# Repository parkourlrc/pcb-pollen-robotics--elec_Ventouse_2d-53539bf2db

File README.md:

# "Ventouse_2d" Electronic Board

"Ventouse_2d" is build from "Themis" as it aims on driving Orbita 2 Dofs. It is paired with boards "Poulpe_2d" that controls 2 BLDC Motors.

## Basically
 - Primarly designed for Reachy 2 gamma.
 - Powered in 24V.
 - Designed with KiCAD 7.

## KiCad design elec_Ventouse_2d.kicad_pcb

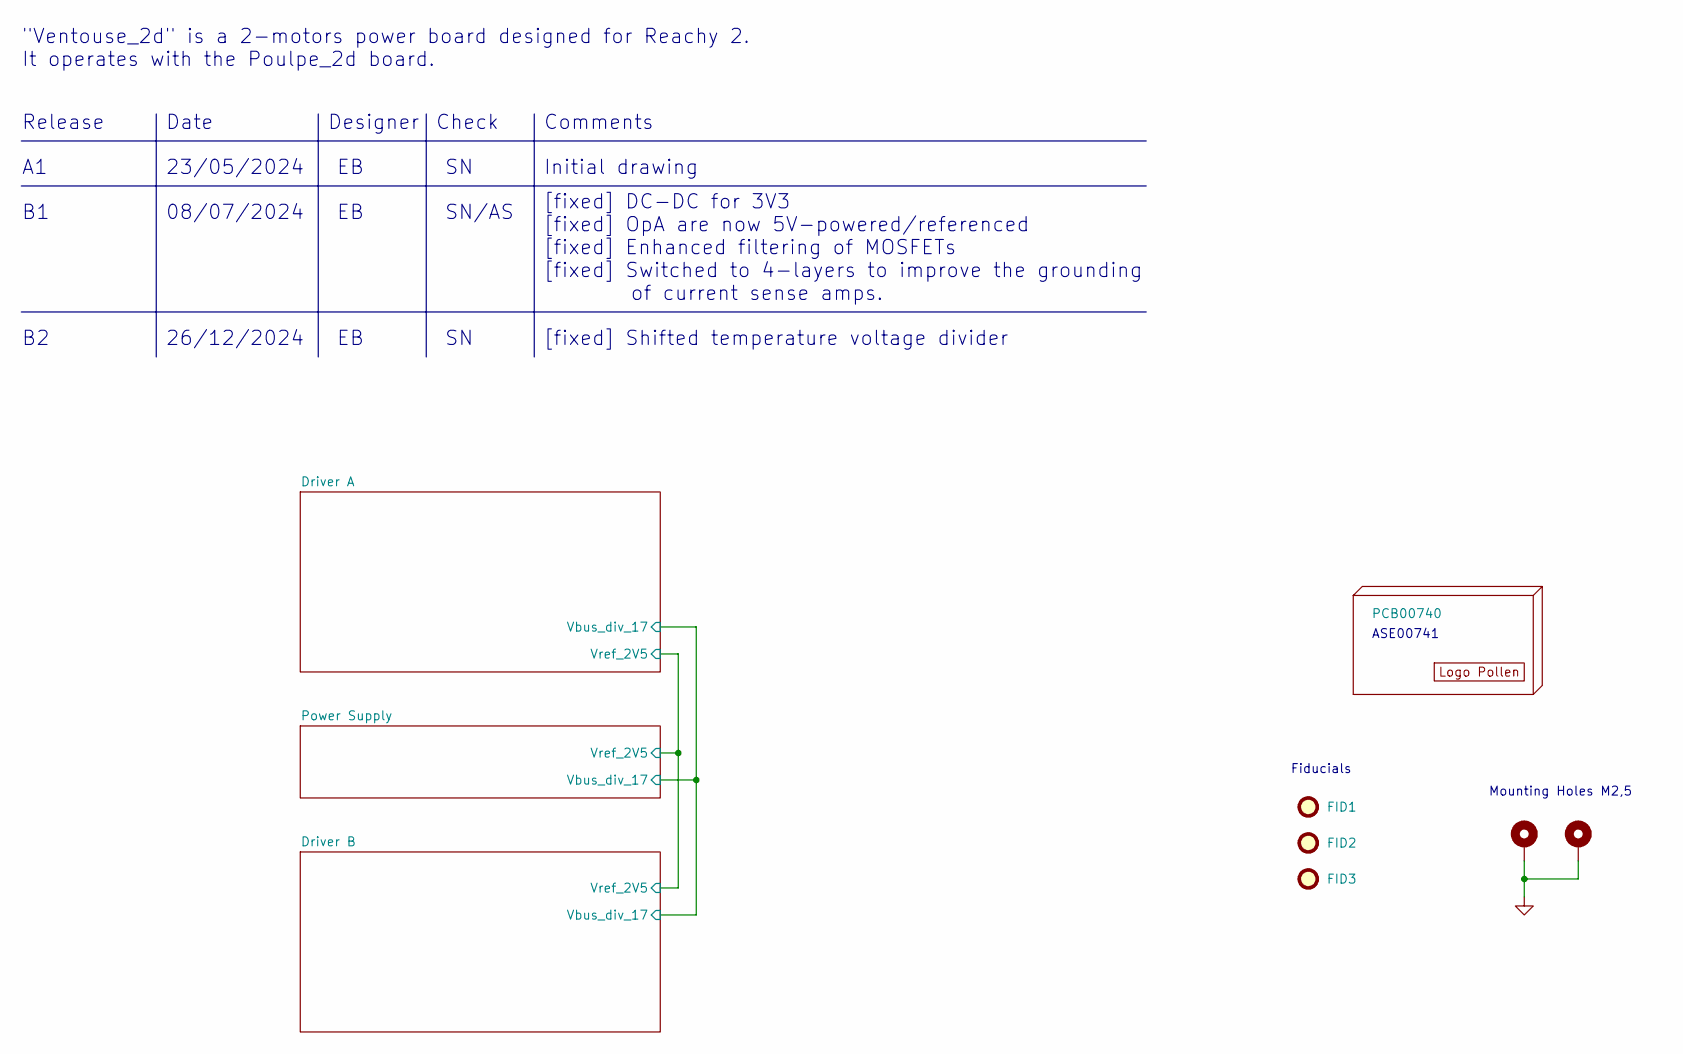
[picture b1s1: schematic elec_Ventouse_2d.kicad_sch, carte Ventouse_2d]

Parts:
FID1, FID2, FID3: DNP Fiducial; Fiducial_1mm_Mask2mm
H1, H2: MountingHole_Pad; MountingHole_2.7mm_M2.5_ISO14580_Pad_TopBottom
H4: PCB00740
H5: DNP Logo Pollen 2021; Logo_Pollen_2021_sq

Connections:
GND: H1.1, H2.1; also elsewhere on the board

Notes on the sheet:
Mounting Holes M2,5
Date
Check
Release
Fiducials
ASE00741
08/07/2024
SN/AS
[fixed] DC-DC for 3V3 [fixed] OpA are now 5V-powered/referenced [fixed] Enhanced filtering of MOSFETs [fixed] Switched to 4-layers to improve the grounding of current sense amps.
Initial drawing
[fixed] Shifted temperature voltage divider
"Ventouse_2d" is a 2-motors power board designed for Reachy 2. It operates with the Poulpe_2d board.
Designer
Comments
23/05/2024
26/12/2024

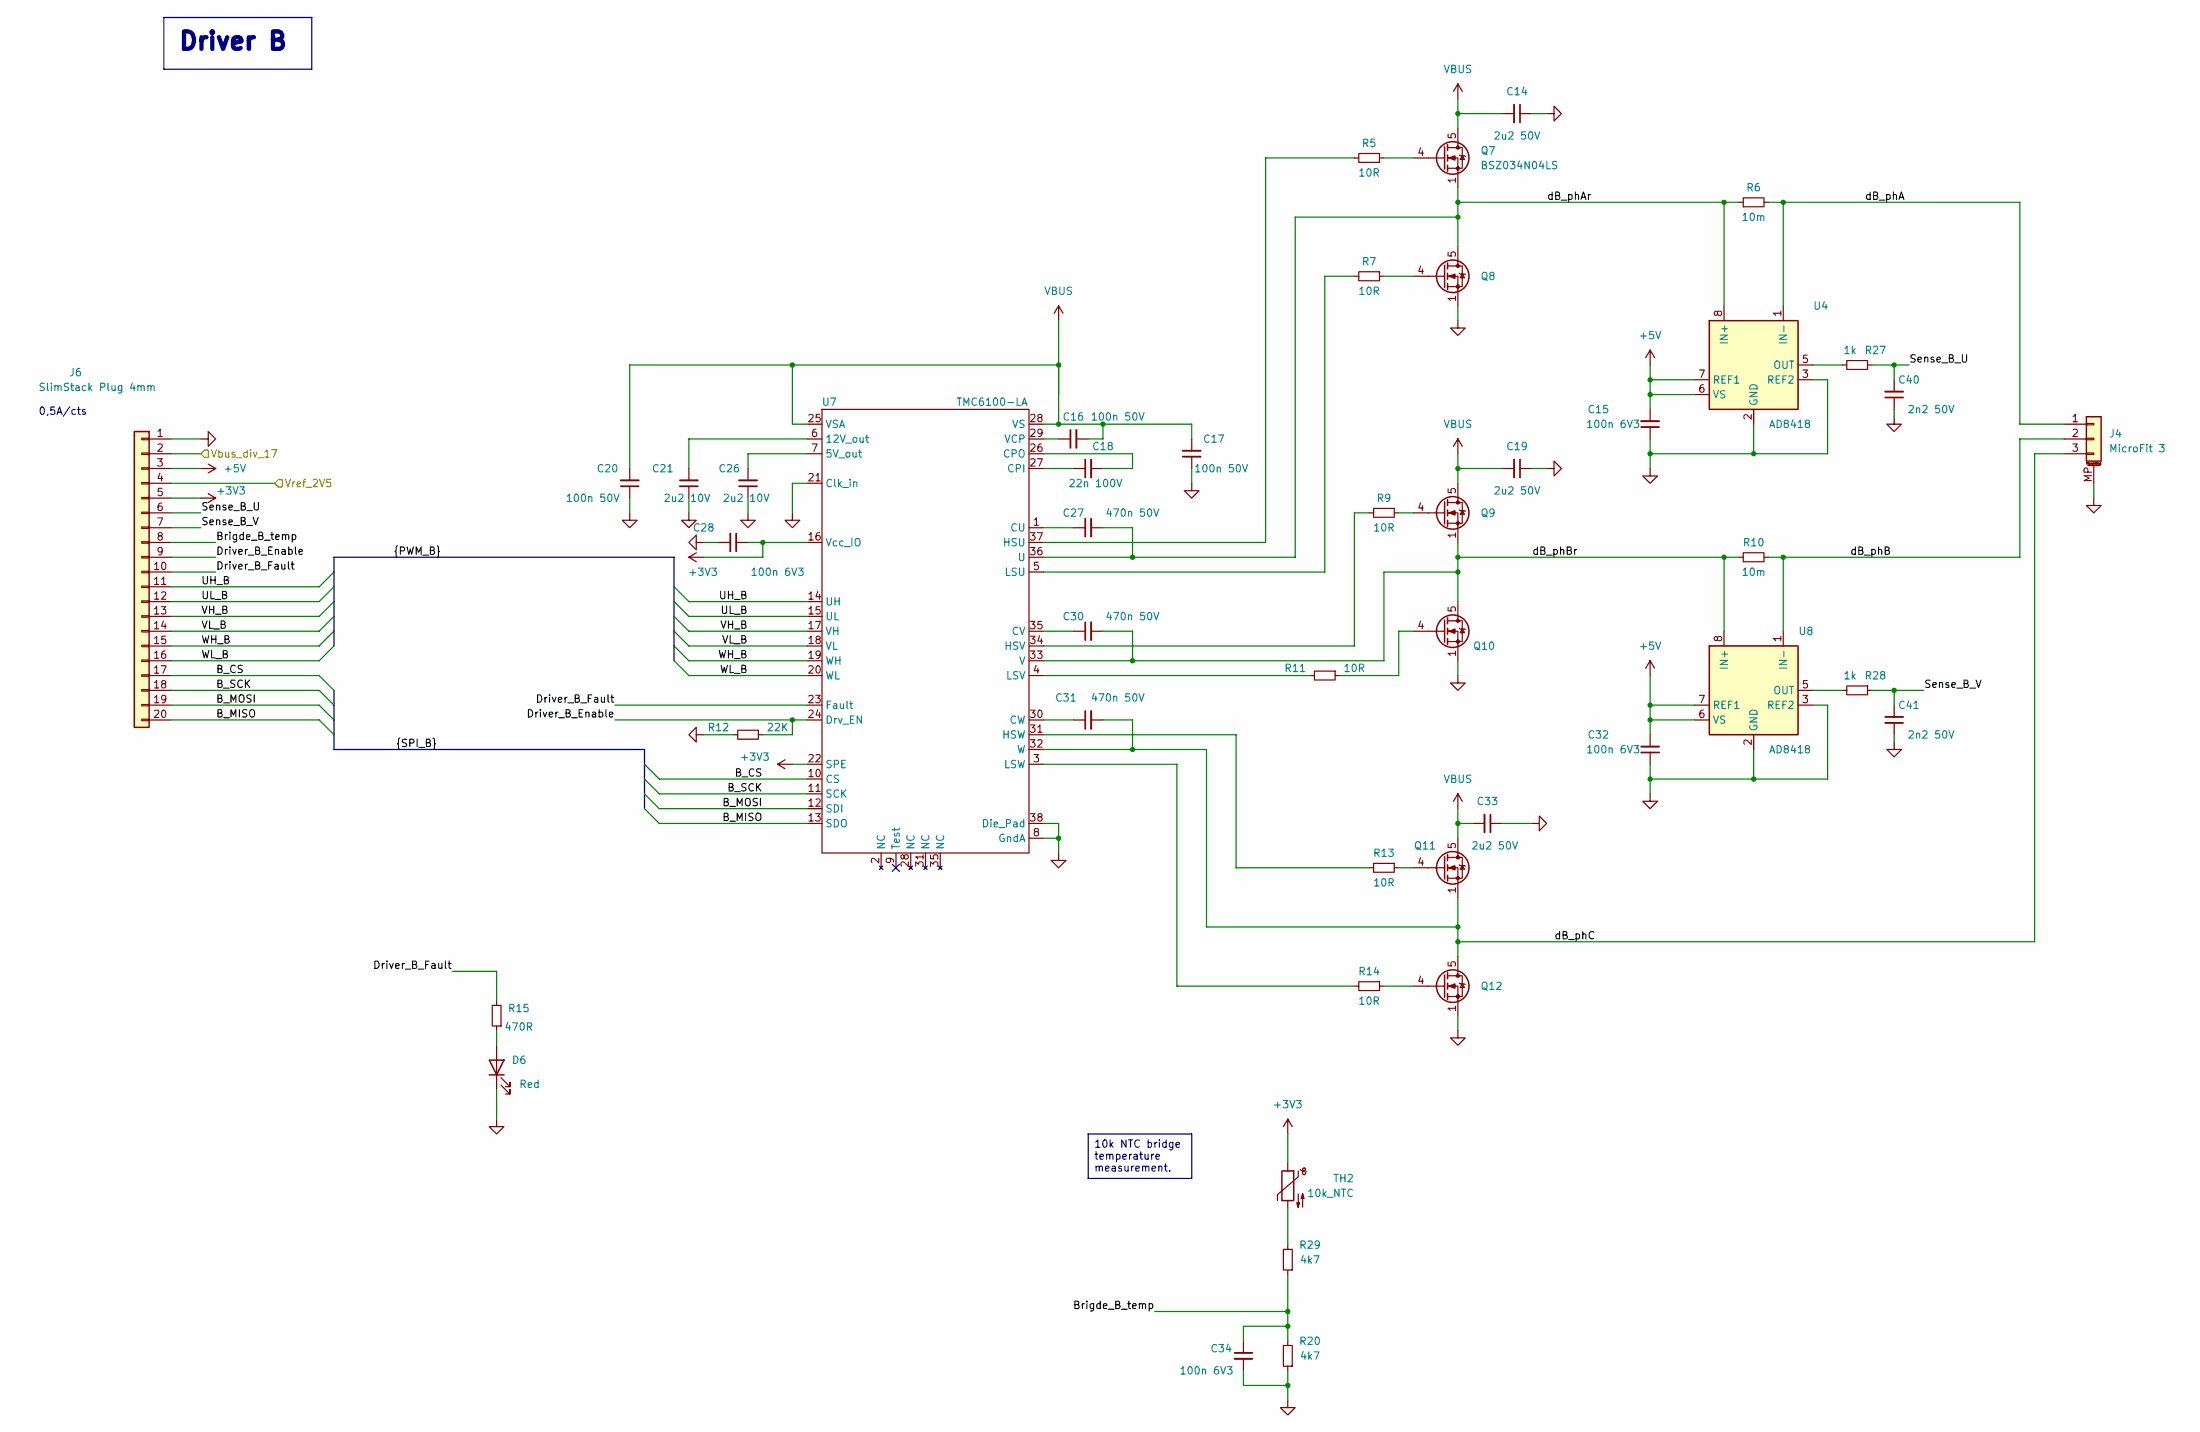
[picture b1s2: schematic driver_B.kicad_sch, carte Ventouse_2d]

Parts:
C14, C19, C33: 2u2 50V; C_1210_3225Metric; LCSC Part C2168116
C15, C28, C32, C34: 100n 6V3; C_0402_1005Metric; LCSC Part C2180552
C16, C17, C20: 100n 50V; C_0402_1005Metric; LCSC Part C307331
C18: 22n 100V; C_0603_1608Metric; LCSC Part C22374871
C21, C26: 2u2 10V; C_0603_1608Metric; LCSC Part C5360777
C27, C30, C31: 470n 50V; C_0603_1608Metric; LCSC Part C513577
C40, C41: 2n2 50V; C_0402_1005Metric; LCSC Part C1531
D6: Red; LED_0603_1608Metric; LCSC Part C3030991
J4: MicroFit 3; Micro-Fit_43650-0310_Horizontal; LCSC Part C2882762
J6: SlimStack Plug 4mm; Molex_SlimStack_539160208; LCSC Part C277596
Q7, Q8, Q9, Q10, Q11, Q12: BSZ034N04LS; PQFN_3.3x3.3mm_-_PG-TDSON-8_FL; LCSC Part C534652
R5, R7, R9, R11, R13, R14: 10R; R_0402_1005Metric; LCSC Part C25077
R6, R10: 10m; Res_1206_ERJ8CWFR010V; LCSC Part C7467248
R12: 22K; R_0402_1005Metric; LCSC Part C25768
R15: 470R; R_0402_1005Metric; LCSC Part C25117
R20, R29: 4k7; R_0402_1005Metric; LCSC Part C25900
R27, R28: 1k; R_0402_1005Metric; LCSC Part C11702
TH2: 10k_NTC; R_0603_1608Metric; LCSC Part C554013
U4, U8: AD8418; SOIC-8_3.9x4.9mm_P1.27mm; LCSC Part C495342
U7: TMC6100-LA; QFN37_7X7_TRI; LCSC Part C3249927

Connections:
+3V3: C28.1, J6.5, TH2.1, U7.16 (Vcc_IO), U7.22 (SPE); also elsewhere on the board
+5V: C15.2, C32.2, J6.3, U4.6 (VS), U4.7 (REF1), U8.6 (VS), U8.7 (REF1); also elsewhere on the board
/Driver A/Vbus_div_17: J6.2; also elsewhere on the board
/Driver A/Vref_2V5: J6.4; also elsewhere on the board
/Driver B/B_CS: J6.17, U7.10 (CS)
/Driver B/B_MISO: J6.20, U7.13 (SDO)
/Driver B/B_MOSI: J6.19, U7.12 (SDI)
/Driver B/B_SCK: J6.18, U7.11 (SCK)
/Driver B/Brigde_B_temp: C34.1, J6.8, R20.2, R29.1
/Driver B/Driver_B_Enable: J6.9, R12.1, U7.24 (Drv_EN)
/Driver B/Driver_B_Fault: J6.10, R15.2, U7.23 (Fault)
/Driver B/Sense_B_U: C40.2, J6.6, R27.1
/Driver B/Sense_B_V: C41.2, J6.7, R28.1
/Driver B/UH_B: J6.11, U7.14 (UH)
/Driver B/UL_B: J6.12, U7.15 (UL)
/Driver B/VH_B: J6.13, U7.17 (VH)
/Driver B/VL_B: J6.14, U7.18 (VL)
/Driver B/WH_B: J6.15, U7.19 (WH)
/Driver B/WL_B: J6.16, U7.20 (WL)
/Driver B/dB_phA: J4.1, R6.2, U4.1 (IN-)
/Driver B/dB_phAr: C27.2, Q7.1 (S), Q8.5 (D), R6.1, U4.8 (IN+), U7.36 (U)
/Driver B/dB_phB: J4.2, R10.2, U8.1 (IN-)
/Driver B/dB_phBr: C30.2, Q9.1 (S), Q10.5 (D), R10.1, U7.33 (V), U8.8 (IN+)
/Driver B/dB_phC: C31.2, J4.3, Q11.1 (S), Q12.5 (D), U7.32 (W)
GND: C14.1, C15.1, C17.1, C19.1, C20.1, C21.1, C26.1, C28.2, C32.1, C33.1, C34.2, C40.1, C41.1, D6.1 (K), J4.MP (MountPin), J6.1, Q8.1 (S), Q10.1 (S), Q12.1 (S), R12.2, R20.1, U4.2 (GND), U4.3 (REF2), U7.8 (GndA), U7.21 (Clk_in), U7.38 (Die_Pad), U8.2 (GND), U8.3 (REF2); also elsewhere on the board
unnamed: D6.2 (A), R15.1
unnamed: Q7.4 (G), R5.1
unnamed: Q8.4 (G), R7.1
unnamed: Q9.4 (G), R9.1
unnamed: Q10.4 (G), R11.1
unnamed: Q11.4 (G), R13.1
unnamed: Q12.4 (G), R14.1
unnamed: R29.2, TH2.2
unnamed: R27.2, U4.5 (OUT)
unnamed: C26.2, U7.7 (5V_out)
unnamed: C21.2, U7.6 (12V_out)
unnamed: C18.1, U7.27 (CPI)
unnamed: C18.2, U7.26 (CPO)
unnamed: C27.1, U7.1 (CU)
unnamed: C30.1, U7.35 (CV)
unnamed: C31.1, U7.30 (CW)
unnamed: R5.2, U7.37 (HSU)
unnamed: R9.2, U7.34 (HSV)
unnamed: R13.2, U7.31 (HSW)
unnamed: R7.2, U7.5 (LSU)
unnamed: R11.2, U7.4 (LSV)
unnamed: R14.2, U7.3 (LSW)
unnamed: C16.1, U7.29 (VCP)
unnamed: R28.2, U8.5 (OUT)
VBUS: C14.2, C16.2, C17.2, C19.2, C20.2, C33.2, Q7.5 (D), Q9.5 (D), Q11.5 (D), U7.25 (VSA), U7.28 (VS); also elsewhere on the board

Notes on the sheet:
0,5A/cts
Driver B
10k NTC bridge temperature measurement.

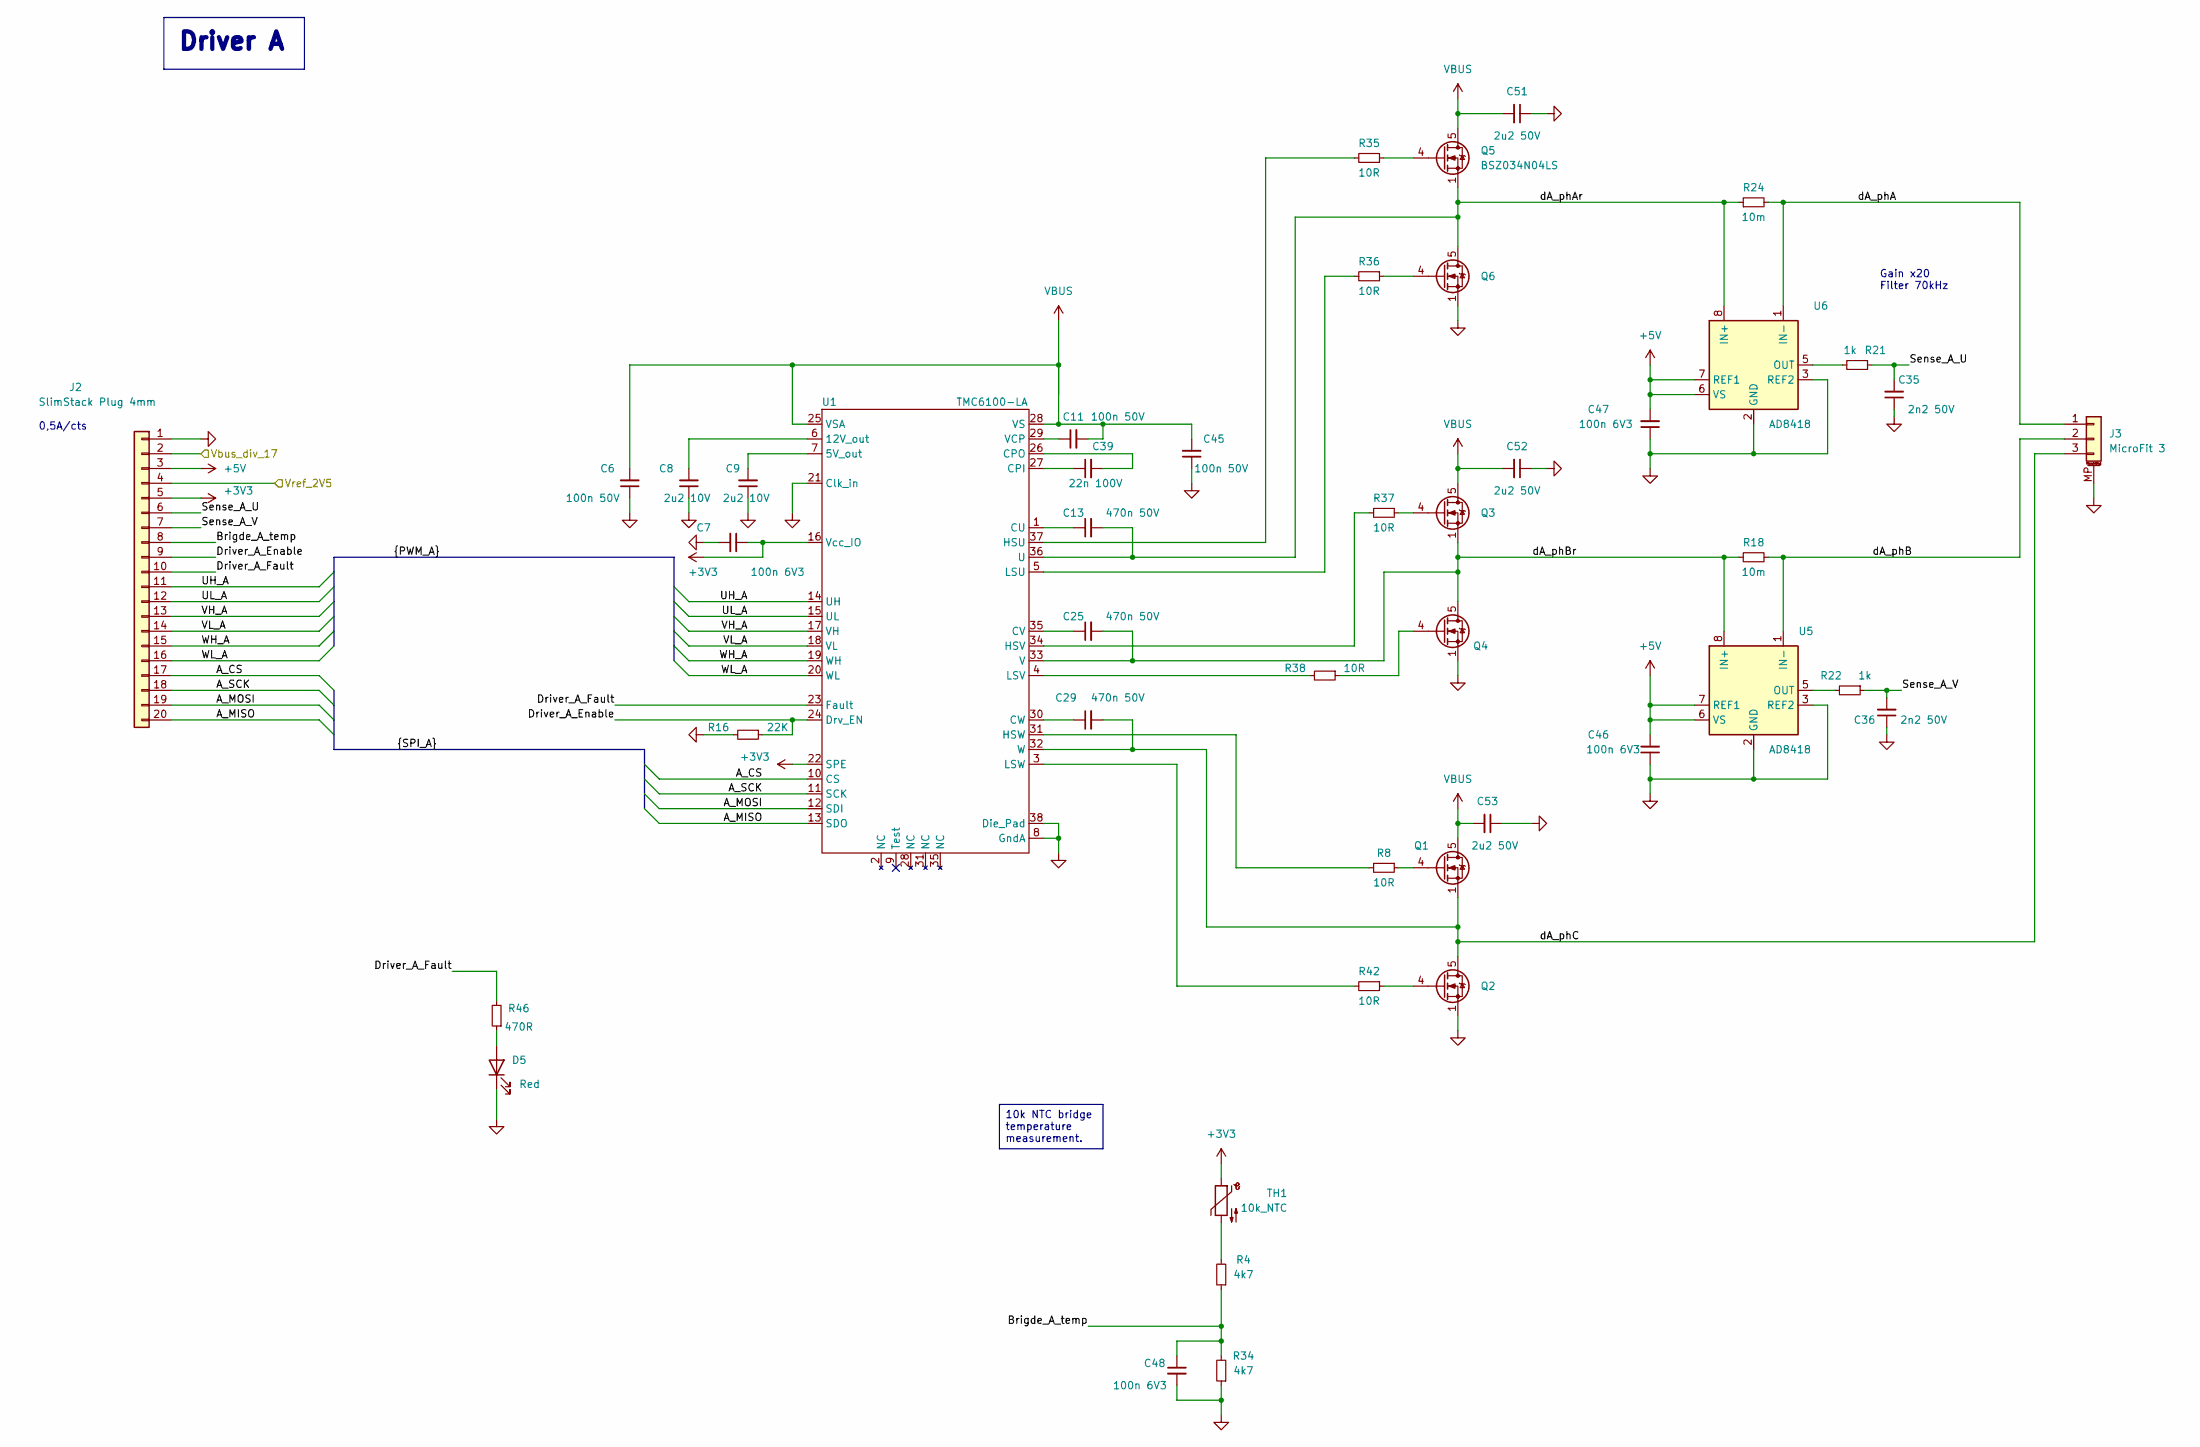
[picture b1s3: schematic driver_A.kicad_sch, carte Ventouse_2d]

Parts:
C6, C11, C45: 100n 50V; C_0402_1005Metric; LCSC Part C307331
C7, C46, C47, C48: 100n 6V3; C_0402_1005Metric; LCSC Part C2180552
C8, C9: 2u2 10V; C_0603_1608Metric; LCSC Part C5360777
C13, C25, C29: 470n 50V; C_0603_1608Metric; LCSC Part C513577
C35, C36: 2n2 50V; C_0402_1005Metric; LCSC Part C1531
C39: 22n 100V; C_0603_1608Metric; LCSC Part C22374871
C51, C52, C53: 2u2 50V; C_1210_3225Metric; LCSC Part C2168116
D5: Red; LED_0603_1608Metric; LCSC Part C3030991
J2: SlimStack Plug 4mm; Molex_SlimStack_539160208; LCSC Part C277596
J3: MicroFit 3; Micro-Fit_43650-0310_Horizontal; LCSC Part C2882762
Q1, Q2, Q3, Q4, Q5, Q6: BSZ034N04LS; PQFN_3.3x3.3mm_-_PG-TDSON-8_FL; LCSC Part C534652
R4, R34: 4k7; R_0402_1005Metric; LCSC Part C25900
R8, R35, R36, R37, R38, R42: 10R; R_0402_1005Metric; LCSC Part C25077
R16: 22K; R_0402_1005Metric; LCSC Part C25768
R18, R24: 10m; Res_1206_ERJ8CWFR010V; LCSC Part C7467248
R21, R22: 1k; R_0402_1005Metric; LCSC Part C11702
R46: 470R; R_0402_1005Metric; LCSC Part C25117
TH1: 10k_NTC; R_0603_1608Metric; LCSC Part C554013
U1: TMC6100-LA; QFN37_7X7_TRI; LCSC Part C3249927
U5, U6: AD8418; SOIC-8_3.9x4.9mm_P1.27mm; LCSC Part C495342

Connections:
+3V3: C7.1, J2.5, TH1.1, U1.16 (Vcc_IO), U1.22 (SPE); also elsewhere on the board
+5V: C46.2, C47.2, J2.3, U5.6 (VS), U5.7 (REF1), U6.6 (VS), U6.7 (REF1); also elsewhere on the board
/Driver A/A_CS: J2.17, U1.10 (CS)
/Driver A/A_MISO: J2.20, U1.13 (SDO)
/Driver A/A_MOSI: J2.19, U1.12 (SDI)
/Driver A/A_SCK: J2.18, U1.11 (SCK)
/Driver A/Brigde_A_temp: C48.1, J2.8, R4.1, R34.2
/Driver A/Driver_A_Enable: J2.9, R16.1, U1.24 (Drv_EN)
/Driver A/Driver_A_Fault: J2.10, R46.2, U1.23 (Fault)
/Driver A/Sense_A_U: C35.2, J2.6, R21.1
/Driver A/Sense_A_V: C36.2, J2.7, R22.1
/Driver A/UH_A: J2.11, U1.14 (UH)
/Driver A/UL_A: J2.12, U1.15 (UL)
/Driver A/VH_A: J2.13, U1.17 (VH)
/Driver A/VL_A: J2.14, U1.18 (VL)
/Driver A/Vbus_div_17: J2.2; also elsewhere on the board
/Driver A/Vref_2V5: J2.4; also elsewhere on the board
/Driver A/WH_A: J2.15, U1.19 (WH)
/Driver A/WL_A: J2.16, U1.20 (WL)
/Driver A/dA_phA: J3.1, R24.2, U6.1 (IN-)
/Driver A/dA_phAr: C13.2, Q5.1 (S), Q6.5 (D), R24.1, U1.36 (U), U6.8 (IN+)
/Driver A/dA_phB: J3.2, R18.2, U5.1 (IN-)
/Driver A/dA_phBr: C25.2, Q3.1 (S), Q4.5 (D), R18.1, U1.33 (V), U5.8 (IN+)
/Driver A/dA_phC: C29.2, J3.3, Q1.1 (S), Q2.5 (D), U1.32 (W)
GND: C6.1, C7.2, C8.1, C9.1, C35.1, C36.1, C45.1, C46.1, C47.1, C48.2, C51.1, C52.1, C53.1, D5.1 (K), J2.1, J3.MP (MountPin), Q2.1 (S), Q4.1 (S), Q6.1 (S), R16.2, R34.1, U1.8 (GndA), U1.21 (Clk_in), U1.38 (Die_Pad), U5.2 (GND), U5.3 (REF2), U6.2 (GND), U6.3 (REF2); also elsewhere on the board
unnamed: D5.2 (A), R46.1
unnamed: Q1.4 (G), R8.1
unnamed: Q2.4 (G), R42.1
unnamed: Q3.4 (G), R37.1
unnamed: Q4.4 (G), R38.1
unnamed: Q5.4 (G), R35.1
unnamed: Q6.4 (G), R36.1
unnamed: R4.2, TH1.2
unnamed: C9.2, U1.7 (5V_out)
unnamed: C8.2, U1.6 (12V_out)
unnamed: C39.1, U1.27 (CPI)
unnamed: C39.2, U1.26 (CPO)
unnamed: C13.1, U1.1 (CU)
unnamed: C25.1, U1.35 (CV)
unnamed: C29.1, U1.30 (CW)
unnamed: R35.2, U1.37 (HSU)
unnamed: R37.2, U1.34 (HSV)
unnamed: R8.2, U1.31 (HSW)
unnamed: R36.2, U1.5 (LSU)
unnamed: R38.2, U1.4 (LSV)
unnamed: R42.2, U1.3 (LSW)
unnamed: C11.1, U1.29 (VCP)
unnamed: R22.2, U5.5 (OUT)
unnamed: R21.2, U6.5 (OUT)
VBUS: C6.2, C11.2, C45.2, C51.2, C52.2, C53.2, Q1.5 (D), Q3.5 (D), Q5.5 (D), U1.25 (VSA), U1.28 (VS); also elsewhere on the board

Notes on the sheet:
Gain x20 Filter 70kHz
0,5A/cts
Driver A
10k NTC bridge temperature measurement.

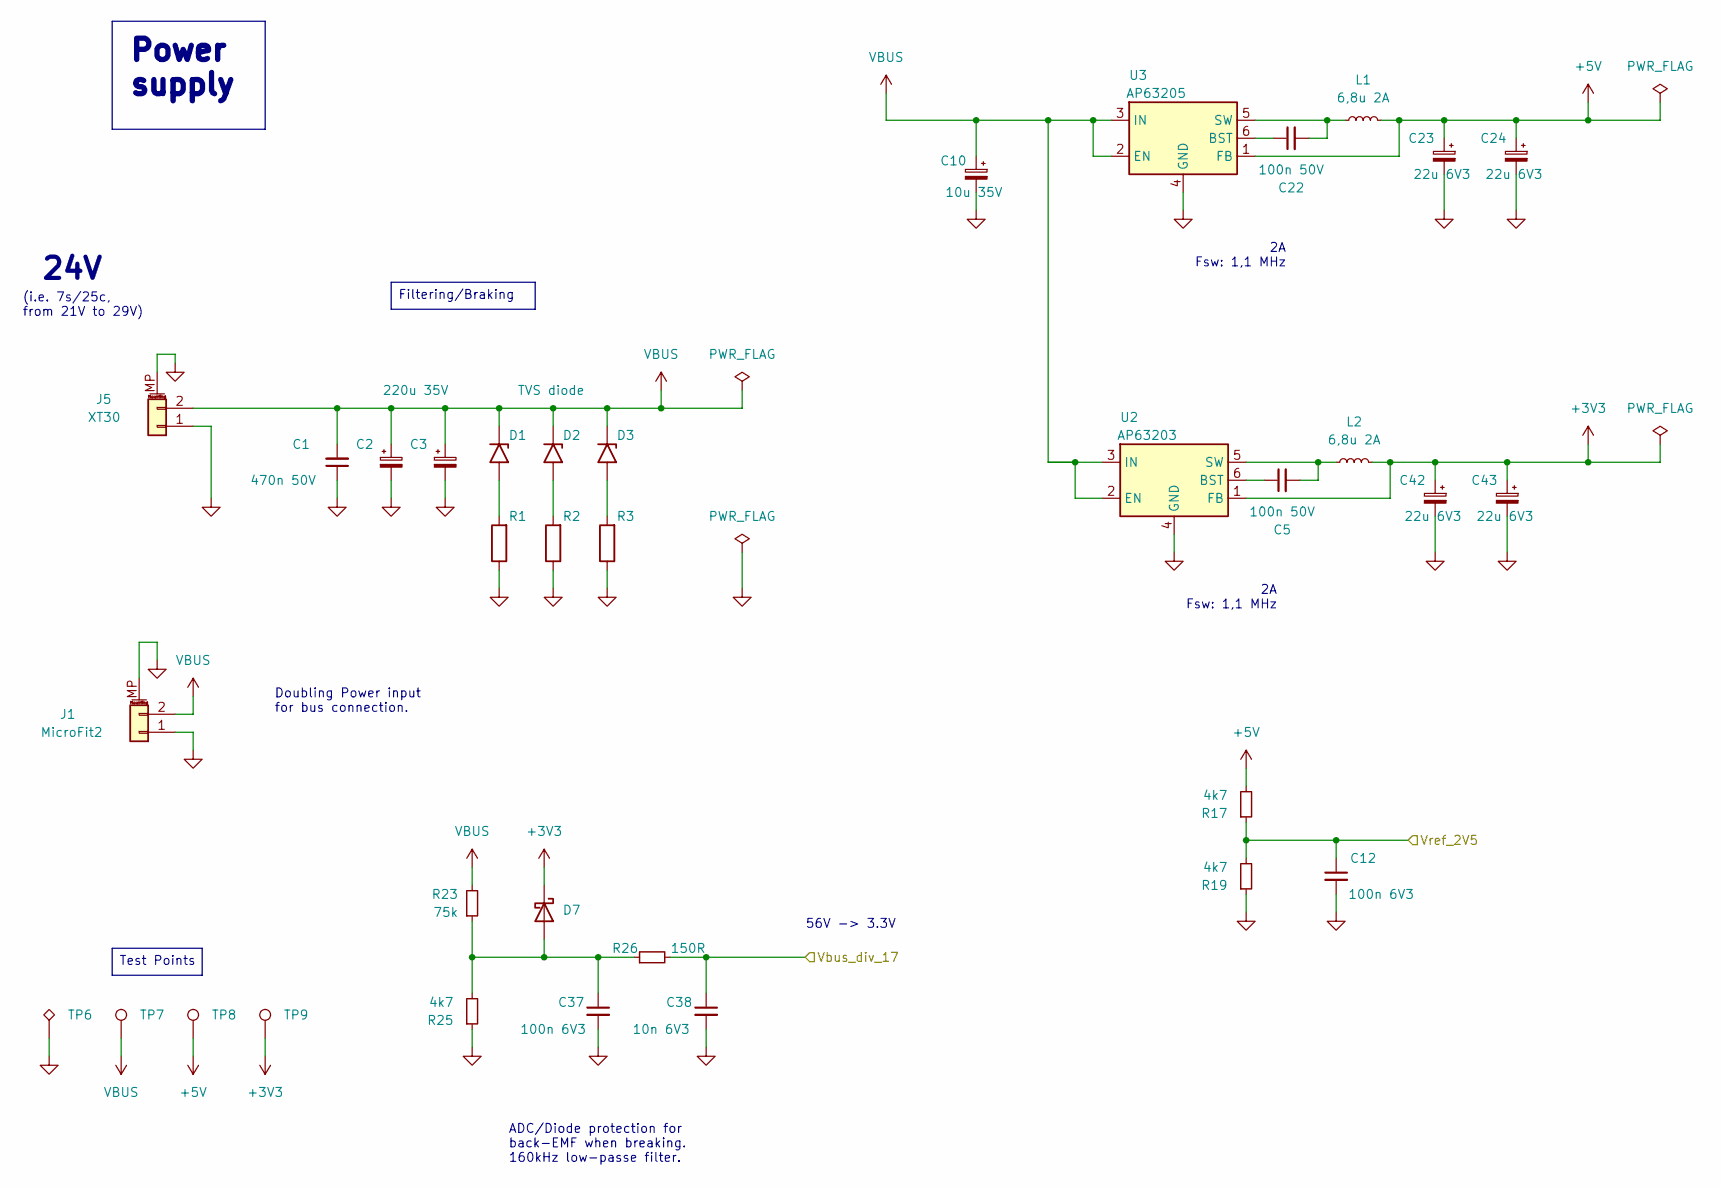
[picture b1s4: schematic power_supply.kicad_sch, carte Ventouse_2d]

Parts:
C1: 470n 50V; C_0603_1608Metric; LCSC Part C513577
C2, C3: 220u 35V; CP_Elec_10x10.5; LCSC Part C72499
C5, C22: 100n 50V; C_0402_1005Metric; LCSC Part C307331
C10: 10u 35V; CP_Elec_6.3x7.7; LCSC Part C72488
C12, C37: 100n 6V3; C_0402_1005Metric; LCSC Part C2180552
C23, C24, C42, C43: 22u 6V3; C_0603_1608Metric; LCSC Part C84419
C38: 10n 6V3; C_0402_1005Metric; LCSC Part C15195
D1, D2, D3: TVS diode; D_SMA; LCSC Part C383018
D7: BAT30KFILM; D_SOD-523; LCSC Part C2926449
J1: MicroFit2; Micro-Fit_43650-0210_Horizontal; LCSC Part C725770
J5: XT30; AMASS_XT30PW-M_1x02_P2.50mm_Horizontal; LCSC Part C431092
L1, L2: 6,8u 2A; L_Bourns_SRN6045TA; LCSC Part C57254
R1, R2, R3: 620m; R_2512W_Pad2.10x3.15mm; LCSC Part C5126252
R17, R19, R25: 4k7; R_0402_1005Metric; LCSC Part C25900
R23: 75k; R_0402_1005Metric; LCSC Part C25798
R26: 150R; R_0402_1005Metric; LCSC Part C25082
TP6: DNP - TestPoint_Alt; TestPoint_THTPad_1.0x1.0mm_Drill0.5mm
TP7, TP8, TP9: DNP - TestPoint; TestPoint_THTPad_D1.0mm_Drill0.4mm
U2: AP63203; TSOT-23-6; LCSC Part C780769
U3: AP63205; TSOT-23-6; LCSC Part C2071056

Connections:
+3V3: C42.1, C43.1, D7.1 (K), L2.1, TP9.1, U2.1 (FB); also elsewhere on the board
+5V: C23.1, C24.1, L1.1, R17.2, TP8.1, U3.1 (FB); also elsewhere on the board
/Driver A/Vbus_div_17: C38.1, R26.2; also elsewhere on the board
/Driver A/Vref_2V5: C12.1, R17.1, R19.2; also elsewhere on the board
GND: C1.1, C2.2, C3.2, C10.2, C12.2, C23.2, C24.2, C37.2, C38.2, C42.2, C43.2, J1.1, J1.MP (MountPin), J5.1, J5.MP (MountPin), R1.1, R2.1, R3.1, R19.1, R25.1, TP6.1, U2.4 (GND), U3.4 (GND); also elsewhere on the board
unnamed: D1.2 (A2), R1.2
unnamed: D2.2 (A2), R2.2
unnamed: D3.2 (A2), R3.2
unnamed: C37.1, D7.2 (A), R23.1, R25.2, R26.1
unnamed: C5.1, U2.6 (BST)
unnamed: C5.2, L2.2, U2.5 (SW)
unnamed: C22.1, U3.6 (BST)
unnamed: C22.2, L1.2, U3.5 (SW)
VBUS: C1.2, C2.1, C3.1, C10.1, D1.1 (A1), D2.1 (A1), D3.1 (A1), J1.2, J5.2, R23.2, TP7.1, U2.2 (EN), U2.3 (IN), U3.2 (EN), U3.3 (IN); also elsewhere on the board

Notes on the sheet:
24V
(i.e. 7s/25c, from 21V to 29V)
Doubling Power input for bus connection.
2A Fsw: 1,1 MHz
ADC/Diode protection for back-EMF when breaking. 160kHz low-passe filter.
56V -> 3.3V
Power supply
Filtering/Braking
Test Points

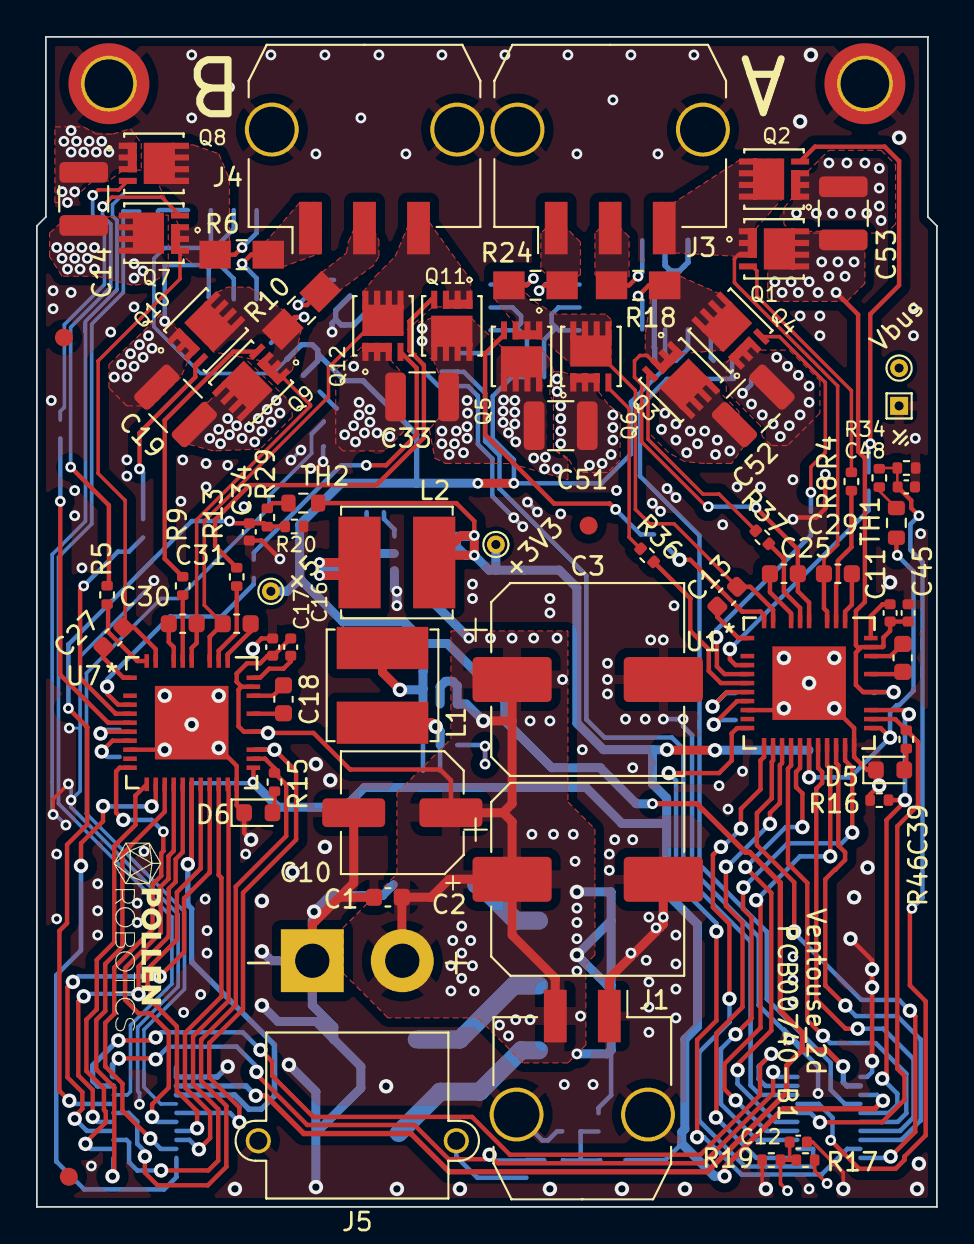
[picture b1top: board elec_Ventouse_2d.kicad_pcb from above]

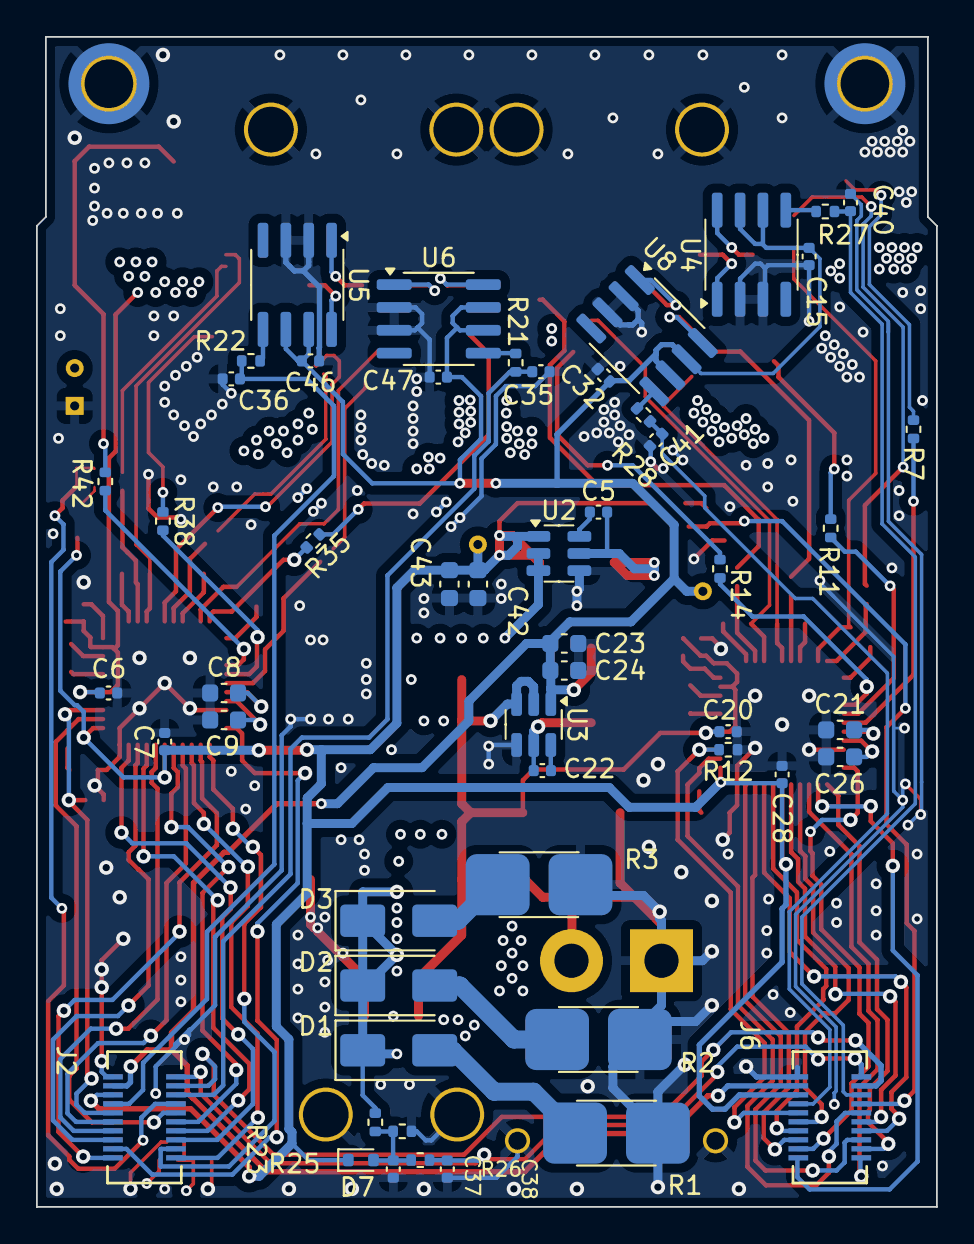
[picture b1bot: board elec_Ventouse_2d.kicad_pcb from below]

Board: 4 copper layers, 50.0 x 65.0 mm, 131 parts (53 on the bottom side), 102 nets.

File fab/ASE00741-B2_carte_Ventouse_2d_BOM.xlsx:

ASE00741 | B2 | Ventouse_2d | 45652
Ref. | Value | Description | Quantity | Man. | Man. Ref.
C1, C13, C25, C27, C29, C30, C31 | 470n 50V | Capa 0603 | 7 | Eurocircuit | GPC0603474
C2, C3 | 220u 35V | Capa diam 10 h 10 | 2 | Multicomp | MCVVT035M221GB3L
C5, C6, C11, C16, C17, C20, C22, C45 | 100n 50V | Capa 0603 | 8 | Eurocircuit | GPC0402104
C7, C12, C15, C28, C32, C34, C37, C46, C47, C48 | 100n 6V3 | Capa 0603 | 10 | Eurocircuit | GPC0402104-16
C8, C9, C21, C26 | 2u2 10V | Capa 0603 | 4 | Eurocircuit | GPC0603225-10-X7R
C10 | 10u 63V | Capa diam. 6,3 / pas 7,7 | 1 | Kemet | EDK106M100A9HAA
C14, C19, C33, C51, C52, C53 | 2u2 50V | Capa 1210 | 6 | Kemet | C1210C225K1RACTU
C18, C39 | 22n 100V | Capa 0603 | 2 | Kemet | C0603C223K1RECAUTO
C23, C24, C42, C43 | 22u 6V3 | Capa 0603 | 4 | Murata | GRM188R61A226ME15D
C35, C36, C40, C41 | 2n2 50V | Capa 0603 | 4 | Eurocircuit | GPC0402222
C38 | 10n 6V3 | Capa 0603 | 1 | Eurocircuit | GPC0402103-16
D1, D2, D3 | TVS diode | Overvoltage Protection | 3 | Vishay | SMAJ26A
D5, D6 | Red | Red LED 0603 | 2 | Wurth | 150060RS75000
D7 | BAT30KFILM | Schottky Diode | 1 | ST Micro | BAT30KFILM
J1 | MicroFit2 | Power Supply Connec. | 1 | Molex | 43650-0210
J2, J6 | SlimStack Plug 4mm |  | 2 | Molex | 53916-0208
J3, J4 | MicroFit 3 | Motor A | 2 | Molex | 43650-0310
J5 | XT30 | Power Supply Connector | 1 | Amass | XT30PW-M
L1, L2 | 6,8u 2A | Inductor 6,8u 2A 6x6 mm | 2 | Bourns | SRN6045TA-6R8M
Q1, Q11 | BSZ034N04LS | Power MOSFET | 2 | Infineon | BSZ034N04LSATMA1
Q2, Q5, Q6, Q7, Q8, Q12 | BSZ034N04LS | Power MOSFET | 6 | Infineon | BSZ034N04LSATMA1
Q3, Q9 | BSZ034N04LS | Power MOSFET | 2 | Infineon | BSZ034N04LSATMA1
Q4, Q10 | BSZ034N04LS | Power MOSFET | 2 | Infineon | BSZ034N04LSATMA1
R1, R2, R3 | 620m | Res. 2512W | 3 | TE Conn. | RLP73K3AR62JTE
R4, R17, R19, R20, R25, R29, R34 | 4k7 | Res. 0603 | 7 | Eurocircuit | GPR04024K7
R5, R7, R8, R9, R11, R13, R14, R35, R36, R37, R38, R42 | 10R | Res. 0603 | 12 | Eurocircuit | GPR040210R
R6, R10, R18, R24 | 10m | R_sense 1206 | 4 | Panasonic | ERJ8CWFR010V
R12, R16 | 22K | Res. 0603 | 2 | Eurocircuit | GPR040222K
R15, R46 | 470R | Res. 0603 | 2 | Eurocircuit | GPR0402470R
R21, R22, R27, R28 | 1k | Res. 0603 | 4 | Eurocircuit | GPR04021K
R23 | 75k | Res. 0603 | 1 | Eurocircuit | GPR040275K
R26 | 150R | Res. 0603 | 1 | Eurocircuit | GPR0402150R
TH1, TH2 | 10k_NTC | Thermistor | 2 | Vishay | NTCS0603E3103FMT
U1, U7 | TMC6100-LA | BLDC Bridge | 2 | Trinamic / AD | TMC6100-LA
U2 | AP63203 | 3V3 DC-DC Buck Converter | 1 | Diodes Inc. | AP63203WU-7
U3 | AP63205 | 5V DC-DC Buck Converter | 1 | Diodes Inc. | AP63205WU-7
U4, U5, U6, U8 | AD8418 | Current Sense OPA | 4 | AD | AD8418WBRZ

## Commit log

2024-04-24 [update] Initial commit.
2024-04-24 [added] Driver B, DRC O.
2024-04-25 [update] adapted from Poulpe 2d, DRC OK.
2024-04-26 [update] Early component placement.
2024-04-29 [update] I do not remember…
2024-05-07 [update] Review méca.
2024-05-10 [update] On-going routing, 2 layers only!
2024-05-13 [update] Driver A full routed. 2 layers!
2024-05-14 [update] Fully routed in 2 layers.
2024-05-15 [update] RC1. Still ERC but all related to thermal pads that I have individualy checked.
2024-05-15 [update] 3d view.
2024-05-16 [update] Tighter PCB on the motor side.
2024-05-20 [update] DRC OK
2024-05-20 [update] Output files.
2024-05-21 [update] Footprint of drivers.
2024-05-22 [update] Better grounding.
2024-05-23 [fixed] Small Eurocircuit corrections.
2024-05-24 [fixed] Top silk component inversion.
2024-07-08 [fix] Post-hardware week debug: noisy current sense.
2024-07-08 [update] Updated schemamtic.
2024-07-09 [update] Just routing
2024-07-09 [added] Dedicated return paths for each Sense.
2024-07-10 [update] Fully routed.
2024-07-10 [update] ERC: warnings only
2024-07-10 [update] DRC OK, ready to check.
2024-07-11 [update] Now in analysis by Eurocircuit.
2024-07-12 [fix] Larger footprints for R_sense.
2024-10-30 [update] still B1, adapted OAR dimensions for EC.
2024-12-26 [fixed] Release B2: shifted temperature voltage divider.
2025-09-12 [update] Almost ready for JLC, just missing the MicroFit 3
2025-09-15 [update] Ready for JLCPCB
2025-09-23 [update] Adding fab folder (sch, gerbers).
